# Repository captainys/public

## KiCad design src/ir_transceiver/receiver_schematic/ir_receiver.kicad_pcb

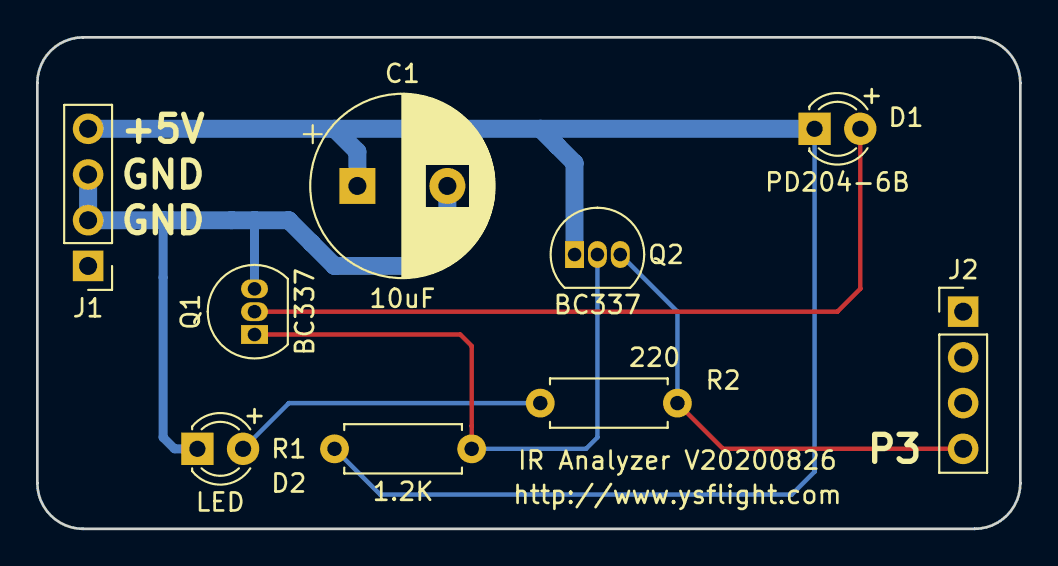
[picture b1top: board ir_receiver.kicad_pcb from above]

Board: 2 copper layers, 54.6 x 27.3 mm, 9 parts (0 on the bottom side), 6 nets.

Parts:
C1: 10uF; CP_Radial_D10.0mm_P5.00mm
D1: PD204-6B; LED_D3.0mm_IRBlack
D2: LED; LED_D3.0mm
J1: Power; PinHeader_1x04_P2.54mm_Vertical
J2: Data; PinHeader_1x04_P2.54mm_Vertical
Q1, Q2: BC337; TO-92_Inline
R1: 1.2K; R_Axial_DIN0207_L6.3mm_D2.5mm_P7.62mm_Horizontal
R2: 220; R_Axial_DIN0207_L6.3mm_D2.5mm_P7.62mm_Horizontal

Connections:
Arduino_+5V: C1.1, D1.1, J1.4, Q2.1, R1.1
Arduino_GND: C1.2, D2.1, J1.2, J1.3, Q1.3
Arduino_Pin3: J2.4, Q2.3, R2.1
unnamed: D1.2, Q1.2
unnamed: D2.2, R2.2
unnamed: Q1.1, Q2.2, R1.2

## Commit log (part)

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2019-04-08 Made the decoder cleaner
2019-04-08 Made decoder shorter
2019-04-09 Adding -append option for T77Save
2019-04-16 Adding support functions
2019-04-17 Added IsInRange in Lattice2d
2019-04-29 Working on Tri to Quad converter
2019-04-29 Working on Tri to Qdom
2019-04-29 Added -raw option in t77load
2019-05-15 38400bps support
2019-05-19 Added -38400bps option
2019-06-16 Fixed loader
2019-06-24 Expanding PNG export.
2019-06-24 Added scaling in PNG export. Bug fix in ysbitmaputil
2019-06-24 Supported transparency in PNG export.
2019-07-09 FM77AV Keyboard Emulator supports Arduino-based emulation.
2019-07-09 Dell desktop couldn't take even 380000bps. Going down to 115200bps.
2019-07-09 Arduino board by default was set to ByteSize=0. Forced it to 8.
2019-07-09 Make it back to 380000bps
2019-07-11 Added 5-byte packet.
2019-07-11 Positive identification of Arduino-based IR emitter. Wait for ready signal after transmission.
2019-07-11 Moved Arduino source from private repo.
2019-07-16 Explicitly control OC1A and OC1B initial state.
2019-07-16 Changed long to int (Arduino int is 16-bit)
2019-07-16 Trying init OC1A/OC1B then start timer.
2019-07-21 Support COM port greater than 9 up to 32
2019-07-23 Prevent RAWREAD going into infintie loop while reading ADDRMARK from unformatted track.
2019-07-24 Simplified Arduino code. Removed pulse-width adjustment (doesn't seem to matter). Removed blinking of PIN13 LED.
2019-07-24 Optimizing for ATmega328. ATmega328 doesn't have a built-in division instruction. Probably a better idea to avoid % (remainder). Also LSL instruction shifts one bit at a time. It doesn't have an inst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
2019-08-04 Changed the way to hook F-BASIC initialization.
2019-08-04 Added M-DOS7 support
2019-08-05 Updated timing.
2019-08-21 Support 16-bit BMP
2019-08-25 Added CPTR command
2019-09-17 Moved FM-7 file system code from non-public to public repo.
2019-09-17 Fix: Unit test was not effective.
2019-09-17 D77write done.
2019-09-18 Speeding up LOADM
2019-09-18 Code cleaning
2019-09-18 Trying to better handle an exception.
2019-09-18 Much cleaner by adding one flag.
2019-09-18 Added error checking.
2019-09-19 D77write does not show verbose info.
2019-10-03 Was not drawing lines.
2019-10-06 Moving auto-typing targets in one directory
2019-10-06 Bug fix
2019-10-18 Meta data things.
2019-10-21 Yet another bug fix of YsShellCrawler
2019-10-30 Added CheapGUI sample
2019-10-30 Adding text input class in CheapGUI library
2019-10-30 Resizing
2019-11-01 Improving Cheap GUI Library
2019-11-03 Making general-purpose IR emitter
2019-11-03 Fixed endianness
2019-11-12 Moved IR transceiver from private repo.
2019-11-12 Added YsLattice2d<T>::CutOut function.
2019-11-12 Fixing Linux build
2019-11-18 Fix macOS 10.15 issue
2019-11-23 IRReceiver
2020-01-11 Fixed build with VS2019.
2020-01-25 Fixed macOS build
2020-02-01 Made D77.cpp independent of FM7Lib.
2020-02-01 D77File::SetRawBinary
2020-02-01 Added D77::GetSector
2020-03-05 Added Global rotation.
2020-03-20 Added Global/Move
2020-04-02 Changed the background data structure.
2020-04-02 Fixed macos build.
2020-04-02 Fixed macosx termination issue.
2020-04-03 Adding GetCurrentPosition
2020-04-03 Adding GetCurrentPosition for ALSA. At this time, it is not complete, but at least can compile.
2020-04-03 Added skeleton for pause and resume.
2020-04-03 Working on pause and resume.
2020-04-09 Working on expand facegroup
2020-04-21 Added LineParser
2020-04-21 Printf -> std::cout
2020-04-24 Fixing FaceGroupExtender
2020-04-24 FaceGroupExtender ready to go.
2020-05-02 Minor fix in D77 utility.
2020-05-04 Working on dha-reducing swapping.
2020-05-24 D77 ForceWriteTrack.
2020-05-24 D77 SetNumTrack
2020-06-17 Finally found a way to play DirectSound when an application window loses focus.
2020-06-26 Limit length of WAV if it exceeds DSBSIZE_MAX.
2020-06-28 Fixed Linux file dialog. It was not recovering from chdir failure.
2020-06-28 Added github workflow.
2020-06-28 Fixed github workflow.
2020-07-06 YM2203 (2612) experiment
2020-07-11 ScaleDiagonal
2020-07-11 Tone Tester
2020-07-13 Added key code for Japanese keyboard.
2020-07-13 Added key mappings for Linux
2020-07-29 Added hole-closure and shrunk-polygon removal in PolygonCrest
2020-08-11 Removed debug output.
2020-08-12 Fixed
2020-08-18 Updating github workflow.
2020-08-18 Renamed workflow script.
2020-08-25 Bug fix. It was inserting a vertex on edges where one of the vertices is on the cutting plane.
2020-08-25 Experimenting FsSetMousePosition.
2020-08-25 Added FsSetMousePosition for macOS.
2020-08-26 Adding FsResizeWindow function.
2020-08-26 Added FsResizeWindow for Linux.
2020-08-27 Made PCB for IR Analyzer
2020-08-28 Working on pipe-axis util.
2020-09-01 Backflow prevention.
2020-09-04 Fixed handling of FSKEY_COLON.
2020-09-10 D77 tool support RAW disk image.
2020-09-10 D77 tool really supports RAW disk image.
2020-10-07 Making YsTraceLineSegmentTemplate
2020-10-07 Make Sheet done.
2020-10-08 MakeSheet function calculates depth based on intersection.
2020-10-10 Adding intersection-reducing edge swapping
2020-10-10 Intersection-Reducing Edge Swapping
2020-11-10 Missing file
2020-11-14 D7CLIENT can work with Disk BIOS Redirector.
2020-11-16 Added reduced-gap option in D7CLIENT, but didn't wotk quite well.
2020-11-16 GAP adjustments
2020-11-20 Fixed D77Server
2020-11-20 Removed in-source build check. Was forcing out-of-source build, but now it allows in-source build. I don't recommend though.
2020-11-20 Fixing build
2020-12-01 Fixed an easy mistake.
2020-12-15 Added yssimplewindow_nownd subdirectory.
2021-01-06 Moved FM7 directory to FM repository.
2021-01-06 Keep 'cheap' libraries with ir_transceiver.
2021-01-06 Simplified 2DRetroMapTool CMakeLists.txt
2021-01-22 Simplifying yssimplesound CMakeLists.txt also adding an alias yssimplesound_platform.
2021-02-03 Restored YS_ALL_BATCH_TEST variable.
2021-02-25 FaceGroup Rename command.
2021-03-23 Fixed wrong face-group initialization.
2021-04-03 Added 8x16 font
2021-04-03 Corrected 8x16 font
2021-04-06 Patch util returns new polygon handles.
2021-05-02 Android template GLESv3 -> GLESv2. Added XK_Scroll_Lock in fssimplewindow for GLX.
2021-05-03 Updated Android instruction.
2021-05-07 Fixed positive-vector calculator.
2021-05-11 GetKeyState -> GetAsyncKeyState
2021-05-19 Updated PolygonCrest readme.
2021-05-25 Liberates keywords from windows.h
2021-06-08 New facegroup commands.
2021-06-10 FACEGROUOP MAKE_ONE_POLYGON
2021-07-01 Remiving this==NULL situations.
2021-07-06 Updated CMakeLists.txt
2021-07-12 Fix build with g++ /O2 option.
2021-08-30 Added variable YS_PUBLIC_LIBRARIES
2021-09-17 CRAWL_A_TO_B mode
2021-09-22 Fixed currentDir calculation in CRAWL_POINT_TO_POINT mode
2021-09-22 Added probe. Fix in MoveAcrossVertex.
2021-09-28 Fixed yssimplesound for macosx in case Objective-C automatic reference counting is turned off.
2021-10-28 Updated fssimplewindow.h for compiler-test server.
2021-11-10 Repair menu Remove Identical Polygons Leaving One and Leaving None.
2021-11-23 Fixed Linux build.
2021-12-06 Polygon Crest new functions.
2021-12-09 Edge-weighted polygon center.
2021-12-18 Adding TexCoord in Ysshell class.
2021-12-18 Added basic functionalities for storing texture coordinates.
2021-12-18 Num key support for Linux.
2021-12-18 Limited support for .OBJ texture coordinate.
2021-12-18 YKKAP
2021-12-20 Legacy ConvexnizeOnePolygon does not use recursion to prevent stack overflow.
2021-12-21 Prevent crash.
2021-12-21 Permissible mode.
2021-12-24 Map XK_grave to FSKEY_TILDA
2021-12-30 Global->Move was not cancelling previous user-interface mode.
2021-12-30 scaling command
2022-01-01 Make yssocket library exportable.
2022-01-01 Fixing Linux and macOS build.
2022-01-16 Export tight bitmap if no mark up.
2022-01-25 Adding support for full screen
2022-01-26 Full-screen support for Linux.
2022-01-26 Tried to add full-screen mode for macOS. Turned out I need to re-create a window to really make it full screen. I don't want to deal with a miserably-failed programming language (Objective-C) any mor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
2022-02-16 Fixed: macOS crashes if 0-length PCM buffer is given to AVAudioPlayerNode.
2022-06-01 Updated yssimplesound
2022-06-02 Left and right volume control.
2022-06-18 Fixing panning
2022-07-15 I am sick and tired of UNIX ld. ld should learn two-pass link or be burnt in the hellfire.
2022-07-15 Fixed macosx build.
2022-08-02 Fixing compiling error
    Fixing "Some warnings being treated as errors" message
2022-08-06 Fixed moving anchored mark up.
2022-08-15 Copy texture coord
2022-09-10 Retro map tool turn off linear interpolation.
2022-09-11 Auto load button.
2022-09-13 Moved 2DRetroMapTool to an independent repository.
2022-09-17 Added function description to YsBound
2022-09-26 Fixing Windows DirectSound streaming.
2022-09-26 Corrected write position after buffer underrun.
2022-10-29 FsShowMouseCursor function.
2022-10-29 FsIsMouseCursorVisible function.
2023-04-03 Fixed file-dialog for macOS. Busy flag was set too late in OnAttach.
2023-04-25 std::hash for YsVec2i and YsVec3i
2023-04-25 Removed a warning.
2023-05-20 yspng supports large bitmap.
2023-06-22 Update fsguidialog.cpp
    Added SetHeight and SetWidth function for buttons
2023-06-22 Update yswin32systemfont.cpp
    Updated windows font
2023-06-22 support OpenGL ARB MSAA
2023-06-22 run RemakePolygonBuffer in single thread
2023-06-22 Correction of spelling mistake
2023-06-23 add msaa setting
2023-06-24 update fopen call in YsBitmap::LoadBmp()
2023-06-24 update sprint call in ysfilename.YsPutExt()
2023-06-24 update call to vsprintf in YsPrintf constructor
2023-06-24 update call to _wfopen in YsFileIO.Fopen()
2023-06-24 use fixed buffSize
2023-06-24 update YsReplaceExtension buffer size, add YsReplaceExtension tests
2023-06-24 exclude CMakeFiles, add test comments
2023-06-24 revise YsPutExt write buffer size, add YsPutExt tests
2023-06-24 DON'T use fixed buffer size in WritetEXtChunk
2023-06-24 add YsPrintf test
2023-06-24 rename test
2023-06-26 enable CRT secure overload defines
2023-06-27 replace kbhit and getch with _ equivalents
2023-08-23 Updated gitignore to exclude the /build directory
2023-09-09 Got the joystick to draw without the lines
2023-09-18 Fix for Linux.
2023-10-13 I think I really fixed the Linux sound player.
2023-10-15 Github workflow uses macos-12.
2023-10-16 snd_pcm_avail_update -> snd_pcm_avail. Hope it fixes occasional sound corruption.
2023-10-17 FsPollDevice does not crash if called before opening a window.
2023-10-18 ALSA playback changed number of output channels from 1 to 2.
2023-10-21 An option to unnecessitate KeepPlaying (sound polling) function in YsSimpleSound library for Linux. The option is by default, turned off. But, can be enabled by defining a macro ALSA_USE_INTERVAL_TIM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
2023-10-21 Allowing YsSoundPlayer recycling.
2023-10-21 Fixed macOS YsSoundPlayer::GetCurrentPosition()
2023-10-21 Fixing test on Linux.
2023-10-21 Fixed build.
2023-10-21 Reinstated YsSimpleSound::StartStreaming with default options.
2023-10-25 Support .WAV file that 'fmt' tag is not the first tag.
2023-11-09 YsSoundPlayer::StreamPlayerReadyToAcceptNextSegment returns error if the given segment is longer than the half of the requested ring-buffer length.
2023-11-30 FsShowMouseCursor(0) for Win32 decreases mouse cursor count down to -2 to assure the cursor does not occasionally pop up.
2023-12-05 Implemented SetVolume for macOSX.
2024-01-10 Synchronized pull-request from tnibert to TOWNSEMU.
2024-09-13 Changed CXX Standard from 11 to 17. Not used anything newer than 11 though.
2024-09-13 Deleted footer from ysclass-library CMake script.
2024-12-05 Removed in-source build rejection.
2024-12-05 Missing include
2024-12-09 Add limited support for .PLY
2024-12-09 PLY writer.
2024-12-09 github workflow macos-12 -> macos-latest
2025-01-28 Reducing warnings.
2025-02-24 Updated FsSimpleWindow for mac
2025-06-12 Adding pipe from path function. I seriously am wondering if I have written this functionality already.
2025-06-13 Pipe with path.
2025-08-07 Making GUI library STL friendly.
2025-09-09 Fixes for FreeBSD compatibility
    - Use 0 instead of NULL when comparing with integer values.
    - Move from old termio.h interface to termios.h.
    - Add missing includes
2025-09-28 Updated CMake minimum version to 3.20
2025-11-25 More options in YsDelaunayTri.
2025-12-14 Set cursor pos test.
